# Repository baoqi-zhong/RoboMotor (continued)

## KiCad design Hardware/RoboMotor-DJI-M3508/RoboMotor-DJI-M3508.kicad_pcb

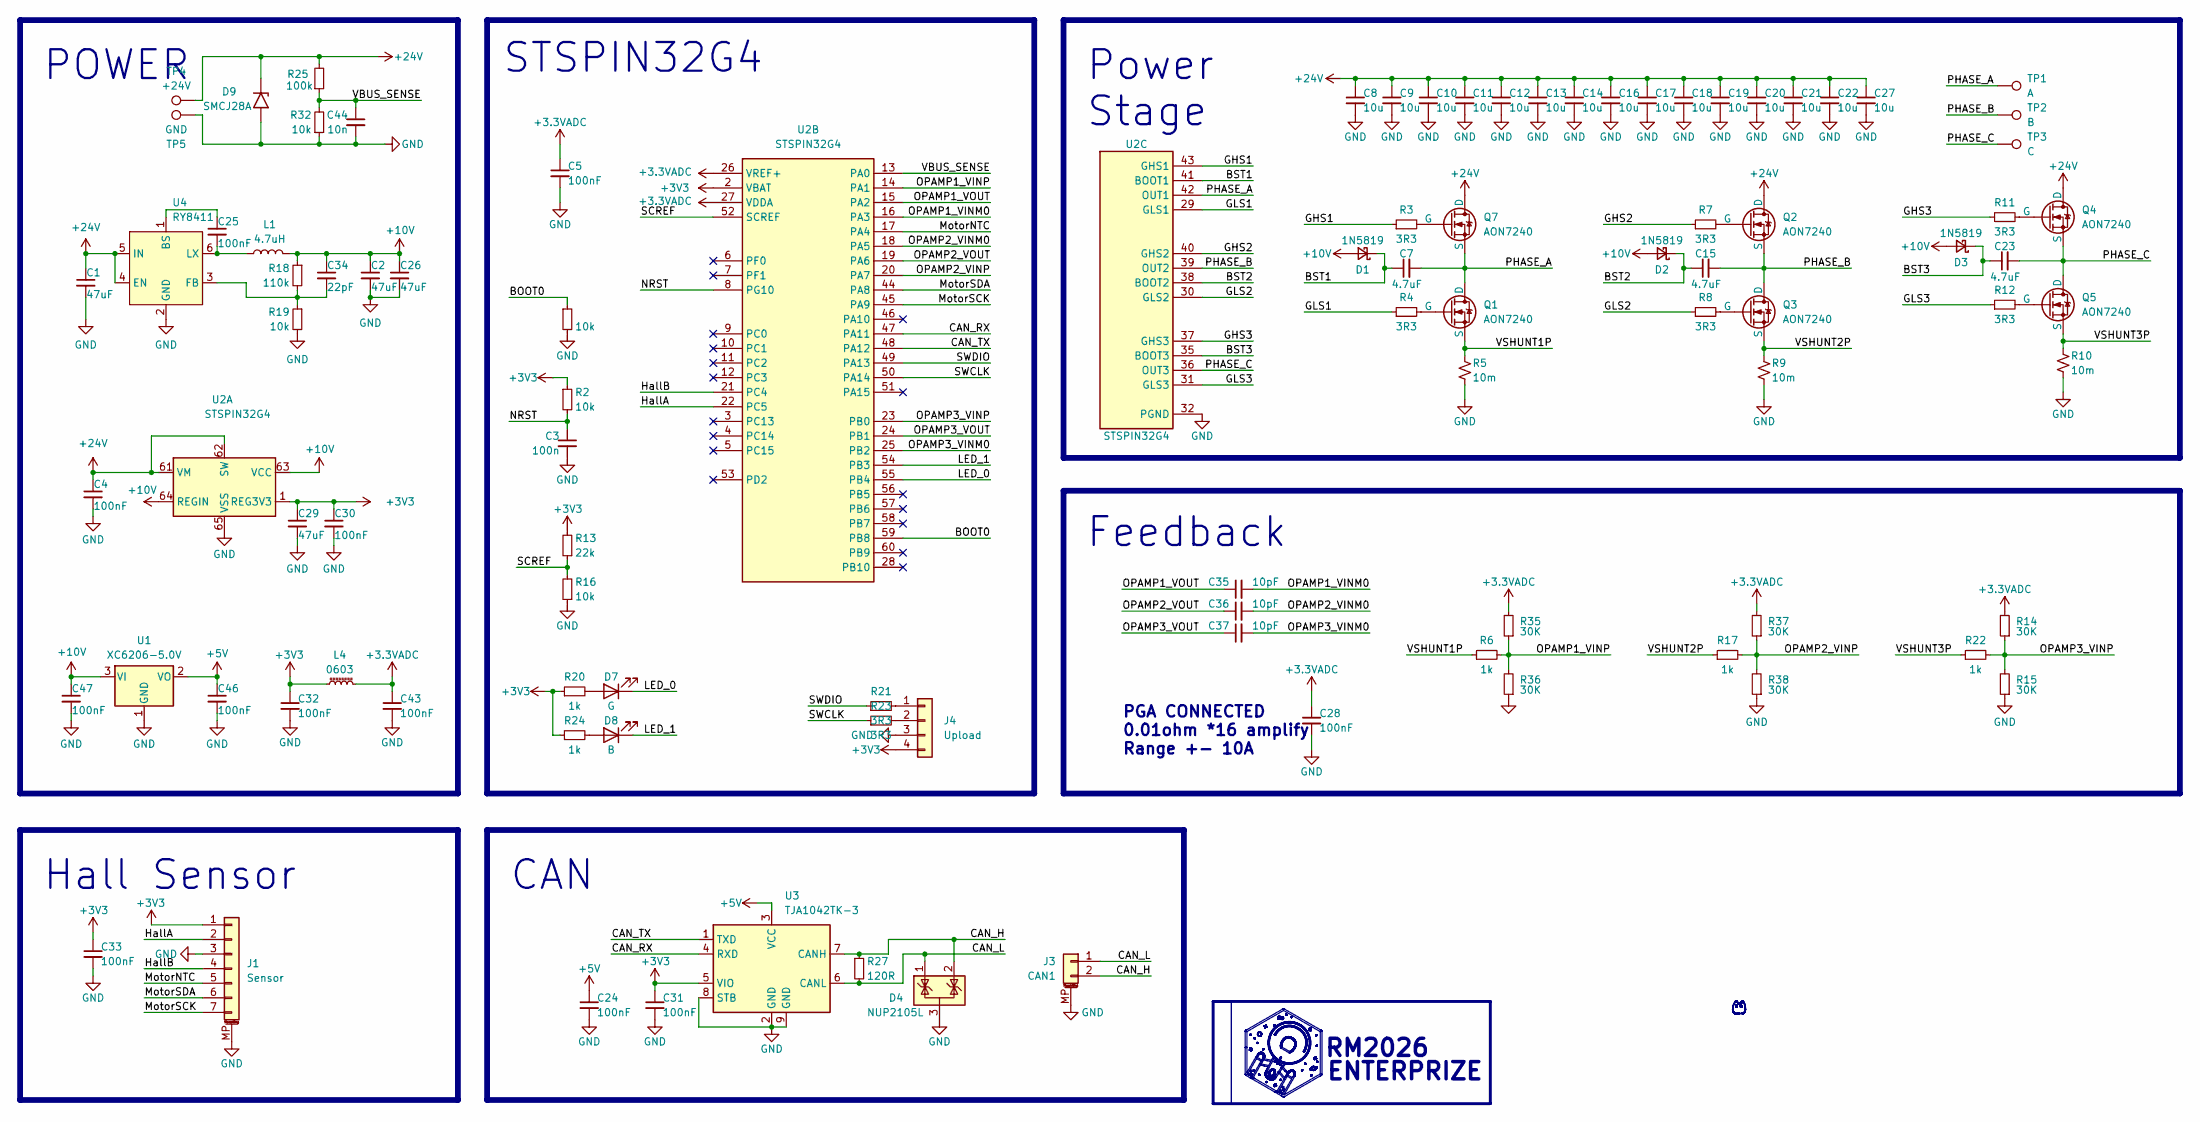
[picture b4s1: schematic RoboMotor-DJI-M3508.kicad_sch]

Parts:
C1: 47uF; C_1206_3216Metric
C2, C26: 47uF; C_0805_2012Metric
C3: 100n; C_0402_1005Metric
C4, C5, C24, C25, C28, C30, C31, C32, C33, C43, C46, C47: 100nF; C_0402_1005Metric
C7, C15, C23: 4.7uF; C_0402_1005Metric
C8, C9, C10, C11, C12, C13, C14, C16, C17, C18, C19, C20, C21, C22, C27: 10u; C_1206_3216Metric
C29: 47uF; C_0603_1608Metric
C34: 22pF; C_0402_1005Metric
C35, C36, C37: 10pF; C_0402_1005Metric
C44: 10n; C_0402_1005Metric
D1, D2, D3: 1N5819; D_SOD-523
D4: NUP2105L; SOT-23
D7: G; LED_0402_1005Metric
D8: B; LED_0402_1005Metric
D9: SMCJ28A; D_SMA
J1: Sensor; Molex_CLIK-Mate_502386-0770_1x07-1MP_P1.25mm_Horizontal
J3: CAN1; JST_GH_SM02B-GHS-TB_1x02-1MP_P1.25mm_Horizontal
J4: Upload; 1.25Upload
L1: 4.7uH; L_Neosid_SMS-ME3015
L4: 0603; L_0603_1608Metric
Q1, Q2, Q3, Q4, Q5, Q7: AON7240; DFN3x3
R1, R2, R16, R19, R32: 10k; R_0402_1005Metric
R3, R4, R7, R8, R11, R12, R21, R23: 3R3; R_0402_1005Metric
R5, R9, R10: 10m; R_1206_3216Metric
R6, R17, R20, R22, R24: 1k; R_0402_1005Metric
R13: 22k; R_0402_1005Metric
R14, R15, R35, R36, R37, R38: 30K; R_0402_1005Metric
R18: 110k; R_0402_1005Metric
R25: 100k; R_0402_1005Metric
R27: 120R; R_0402_1005Metric
TP1: A; TestPoint_Pad_2.0x2.0mm
TP2: B; TestPoint_Pad_2.0x2.0mm
TP3: C; TestPoint_Pad_2.0x2.0mm
TP4: +24V; TestPoint_Pad_2.5x2.5mm
TP5: GND; TestPoint_Pad_2.5x2.5mm
U1: XC6206-5.0V; SOT-23-3
U2: STSPIN32G4; QFN-64-1EP_9x9mm_P0.5mm_EP4.35x4.35mm
U3: TJA1042TK-3; DFN-8-1EP_3x3mm_P0.65mm_EP1.55x2.4mm
U4: RY8411; SOT-23-6

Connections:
+3.3VADC: C5.1, C28.1, C43.1, L4.2, R14.2, R35.2, R37.2, U2.26 (VREF+), U2.27 (VDDA)
+3V3: C29.1, C30.1, C31.1, C32.1, C33.1, J1.1, J4.4, L4.1, R2.1, R13.2, R20.1, R24.1, U2.1 (REG3V3), U2.2 (VBAT), U3.5 (VIO)
+5V: C24.1, C46.1, U1.2 (VO), U3.3 (VCC)
+10V: C2.1, C26.1, C34.1, C47.1, D1.2 (A), D2.2 (A), D3.2 (A), L1.2, R18.1, U1.3 (VI), U2.63 (VCC), U2.64 (REGIN)
+24V: C1.1, C4.1, C8.1, C9.1, C10.1, C11.1, C12.1, C13.1, C14.1, C16.1, C17.1, C18.1, C19.1, C20.1, C21.1, C22.1, C27.1, D9.1 (A1), Q2.1 (D), Q4.1 (D), Q7.1 (D), R25.2, TP4.1, U2.61 (VM), U2.62 (SW), U4.4 (EN), U4.5 (IN)
/BOOT0: R1.1, U2.59 (PB8)
/BST1: C7.1, D1.1 (K), U2.41 (BOOT1)
/BST2: C15.1, D2.1 (K), U2.38 (BOOT2)
/BST3: C23.1, D3.1 (K), U2.35 (BOOT3)
/CAN_H: D4.2 (K), J3.2, R27.1, U3.7 (CANH)
/CAN_L: D4.1 (K), J3.1, R27.2, U3.6 (CANL)
/CAN_RX: U2.47 (PA11), U3.4 (RXD)
/CAN_TX: U2.48 (PA12), U3.1 (TXD)
/GHS1: R3.1, U2.43 (GHS1)
/GHS2: R7.1, U2.40 (GHS2)
/GHS3: R11.1, U2.37 (GHS3)
/GLS1: R4.1, U2.29 (GLS1)
/GLS2: R8.1, U2.30 (GLS2)
/GLS3: R12.1, U2.31 (GLS3)
/HallA: J1.2, U2.22 (PC5)
/HallB: J1.4, U2.21 (PC4)
/LED_0: D7.1 (K), U2.55 (PB4)
/LED_1: D8.1 (K), U2.54 (PB3)
/MotorNTC: J1.5, U2.17 (PA4)
/MotorSCK: J1.7, U2.45 (PA9)
/MotorSDA: J1.6, U2.44 (PA8)
/NRST: C3.1, R2.2, U2.8 (PG10)
/OPAMP1_VINM0: C35.2, U2.16 (PA3)
/OPAMP1_VINP: R6.2, R35.1, R36.2, U2.14 (PA1)
/OPAMP1_VOUT: C35.1, U2.15 (PA2)
/OPAMP2_VINM0: C36.2, U2.18 (PA5)
/OPAMP2_VINP: R17.2, R37.1, R38.2, U2.20 (PA7)
/OPAMP2_VOUT: C36.1, U2.19 (PA6)
/OPAMP3_VINM0: C37.2, U2.25 (PB2)
/OPAMP3_VINP: R14.1, R15.2, R22.2, U2.23 (PB0)
/OPAMP3_VOUT: C37.1, U2.24 (PB1)
/PHASE_A: C7.2, Q1.1 (D), Q7.3 (S), TP1.1, U2.42 (OUT1)
/PHASE_B: C15.2, Q2.3 (S), Q3.1 (D), TP2.1, U2.39 (OUT2)
/PHASE_C: C23.2, Q4.3 (S), Q5.1 (D), TP3.1, U2.36 (OUT3)
/SCREF: R13.1, R16.2, U2.52 (SCREF)
/SWCLK: R23.1, U2.50 (PA14)
/SWDIO: R21.1, U2.49 (PA13)
/VBUS_SENSE: C44.1, R25.1, R32.2, U2.13 (PA0)
/VSHUNT1P: Q1.3 (S), R5.1, R6.1
/VSHUNT2P: Q3.3 (S), R9.1, R17.1
/VSHUNT3P: Q5.3 (S), R10.1, R22.1
GND: C1.2, C2.2, C3.2, C4.2, C5.2, C8.2, C9.2, C10.2, C11.2, C12.2, C13.2, C14.2, C16.2, C17.2, C18.2, C19.2, C20.2, C21.2, C22.2, C24.2, C26.2, C27.2, C28.2, C29.2, C30.2, C31.2, C32.2, C33.2, C43.2, C44.2, C46.2, C47.2, D4.3 (A), D9.2 (A2), J1.3, J1.MP (MountPin), J3.MP (MountPin), J4.3, R1.2, R5.2, R9.2, R10.2, R15.1, R16.1, R19.2, R32.1, R36.1, R38.1, TP5.1, U1.1 (GND), U2.32 (PGND), U2.65 (VSS), U3.2 (GND), U3.8 (STB), U3.9 (GND), U4.2 (GND)
unnamed: D7.2 (A), R20.2
unnamed: D8.2 (A), R24.2
unnamed: J4.1, R21.2
unnamed: J4.2, R23.2
unnamed: Q1.2 (G), R4.2
unnamed: Q2.2 (G), R7.2
unnamed: Q3.2 (G), R8.2
unnamed: Q4.2 (G), R11.2
unnamed: Q5.2 (G), R12.2
unnamed: Q7.2 (G), R3.2
unnamed: C25.1, U4.1 (BS)
unnamed: C34.2, R18.2, R19.1, U4.3 (FB)
unnamed: C25.2, L1.1, U4.6 (LX)

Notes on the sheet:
Power Stage
CAN
POWER
PGA CONNECTED 0.01ohm *16 amplify Range +- 10A
RM2026
Feedback
Hall Sensor
STSPIN32G4
ENTERPRIZE

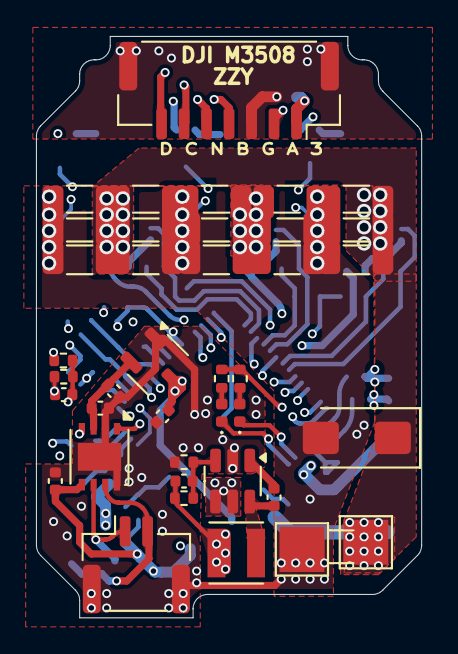
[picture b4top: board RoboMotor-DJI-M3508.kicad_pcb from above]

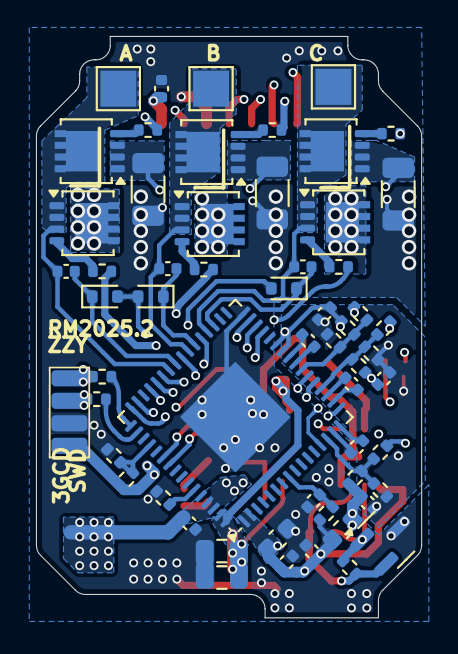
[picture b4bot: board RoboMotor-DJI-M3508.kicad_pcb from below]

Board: 6 copper layers, 21.4 x 32.3 mm, 98 parts (58 on the bottom side), 60 nets.

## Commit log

2026-03-24 Add Hardware PCB
2026-03-24 Update Cover
2026-03-24 Add MIT License
2026-03-25 Update README & Submodule
2026-03-27 GIM6010 CNC Reverse Engineering
